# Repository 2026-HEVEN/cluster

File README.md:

# HEVEN Cluster 펌웨어

**2026 영광 대회 · 계기 클러스터(Instrument Cluster)** — ESP32가 CAN/BLE로 차량 상태(속도·전압·SOC·온도·에러)를 **받아서** LCD에 표현하고, 계기판 버튼 입력을 VCU로 보냅니다. PCB V3에서는 VESS PWM도 Cluster가 직접 출력합니다. VCU와 달리 **안전 임계가 약한 표시 전용 보드**입니다.

> 🤖 **AI 에이전트/팀원은 [`AGENTS.md`](AGENTS.md)를 먼저 읽으세요** — 무엇을 고쳐도 되고 무엇을 건드리면 안 되는지 규칙이 있습니다.

---

## 한눈에

- **스택**: PlatformIO + Arduino-ESP32, TWAI(CAN), ILI9341 LCD. 화면은 **패널 독립적 1bpp 프레임버퍼**(위젯이 그림) + `display_blit`(ILI9341로 blit)
- **구조**: 잠긴 코어(CAN·프레임버퍼·blit) + 팀원이 채우는 순수 모듈(`src/modules/`). VCU와 **동일한 2층 설계**지만 안전 FSM·50ms 라이프 태스크가 없고 CAN은 **수신(RX) 위주**입니다.
- **상태**: ESP32 빌드 성공, 호스트 native 테스트 111개 통과

## 사용자 문서

- [계기판 기능 및 한계](docs/ui_report/REPORT.md)
- [계기판 사용설명서](docs/ui_report/USER_MANUAL.md)
- [추가 CAN 정보 및 실차 확인 사항](docs/ui_report/CAN_DATA_REQUIRED.md)

## 빠른 시작

```bash
# 1. 이 레포를 깨끗한 위치에 클론
git clone https://github.com/2026-HEVEN/cluster.git
cd cluster

# 2. PlatformIO 설치 (한 번만) — VS Code면 PlatformIO IDE 확장 설치로 대체 가능
uv tool install platformio      # 또는: pipx install platformio

# 3. 노트북에서 테스트 (하드웨어 불필요)
pio test -e native

# 4. 보드에 빌드 & 업로드 (ESP32 연결 상태에서)
pio run -e esp32dev -t upload
```

> 🧪 **테스트가 처음이거나 Windows 사용자라면** → 노션 [펌웨어 테스트 실행 방법](https://www.notion.so/390913e532e68199a9b5e340b73e9e71) 참고. AI에 복붙할 프롬프트 + "이렇게 나오면 성공" 출력 예시 + Windows(WSL2/MinGW) 셋업까지 있습니다. (보드 업로드는 Windows도 그냥 되고, `native` 단위테스트만 host 컴파일러가 필요해요.)

> ℹ️ 모터컨트롤러 값은 MCU→VCU 피드백 프레임을 Cluster가 같은 CAN 버스에서 수신합니다. BMS SOC는 `LWS-1608` BLE BMS에 Cluster ESP32가 직접 연결해 표시용 telemetry로만 읽습니다.
> ℹ️ 계기판 속도 표시는 VCU가 내부 `vehicle_speed_compute()`로 산출한 단일 차량속도 프레임 `0x1803C0D0`을 사용합니다. 이 값은 전륜 기준 보정 로직을 거친 `km/h x 10` 값이며, Cluster는 다시 네 바퀴 평균을 내지 않습니다.
> ℹ️ GPS Lap Start는 현재 GNSS fix 위치를 출발점으로 저장합니다. 이후 VCU 단일 차량속도 `0.5 km/h` 초과가 `150ms` 이상 지속되면 랩타이머를 시작하고, 다시 출발점 반경 `2.0m` 안으로 들어오면 랩을 갱신합니다.

## 현재 하드웨어 핀맵 (PCB V3)

| 구분 | 기능 | ESP32 GPIO | 연결/동작 |
|------|------|------------|-----------|
| CAN | TXD | GPIO13 | CAN 트랜시버 TXD |
| CAN | RXD | GPIO14 | CAN 트랜시버 RXD |
| LCD ILI9341 | CS / RST / DC | GPIO23 / 22 / 21 | LCD 제어 |
| LCD / Touch SPI | MOSI / SCK / MISO | GPIO17 / 18 / 35 | 공용 SPI |
| LCD Touch XPT2046 | T_CS | GPIO16 | Touch chip select |
| GPS ZED-F9P | RX / TX / PPS | GPIO25 / 26 / 27 | 115200 baud NMEA/UBX, RTCM3 및 PPS |
| VESS | PWM | GPIO4 | 반전 MOSFET 구동, 50Hz 고정. 외부 RX-TH에는 1~2ms High 펄스 출력 |
| HMI | TV | GPIO32 | 토글 스위치, PCB 외부 10k 풀업, ON=LOW |
| HMI | Paddock | GPIO33 | 토글 스위치, PCB 외부 10k 풀업, ON=LOW |
| HMI | HOME | GPIO19 | 순간 푸시 버튼, PCB 외부 10k 풀업, ON=LOW |
| HMI | GPS Lap | GPIO5 | 순간 푸시 버튼, PCB 외부 10k 풀업, ON=LOW |
| HMI | Regen bit0 / bit1 | GPIO36 / 39 | 로터리, ON=LOW, 두 핀 모두 외부 풀업 필요 |
| Sense | START_IN | GPIO34 | 시동 전원 감지 ADC. 버튼 출력 핀이 아님 |

GPS TX2는 PCB V3에서 Cluster ESP32 `GPIO25` RX에 연결한다.

Cluster는 부팅 시 ZED-F9P UART1/UART2가 460800 baud로 설정되어 있더라도 UBX 설정으로 115200 baud로 낮춘 뒤 통신한다. NMEA가 끊기면 115200 baud 복구를 다시 시도하므로, 같은 GPS TX에 연결된 외부 로거도 115200 baud로 유지할 수 있다.

RTK 사용 시 Cluster ESP32가 Wi-Fi로 NTRIP caster에 접속하고, 수신한 RTCM3 바이트를 가공 없이 `GPIO26` UART TX로 ZED-F9P RX2에 전달한다. 실제 Wi-Fi/NTRIP 계정정보는 `include/ntrip_secrets.h`에 넣고 Git에는 올리지 않는다. `include/ntrip_secrets.example.h`를 복사해서 사용한다.

Cluster는 ZED-F9P RMC의 Speed Over Ground를 km/h로 변환해 새 RMC마다 Extended CAN `0x18F9FFC0`으로 송신한다. 속도는 0.01 km/h/bit이며 같은 프레임에 RMC fresh, GPS fix, RTK FLOAT/FIXED, speed valid, GGA quality와 RMC age를 포함한다. 상세 byte layout은 `docs/CAN_PROTOCOL.md`를 따른다.

회생제동 입력은 GPIO36/39 두 비트 로터리다. 0단은 OFF, 1~3단은 모두 같은 ON 요청으로 인코딩한다. 실제 회생 가능 여부와 전류 제한은 VCU가 최종 판단한다.

GPIO15는 현재 펌웨어에서 사용하지 않는다. GPIO15는 strapping pin이므로 외부 회로가 부팅 순간 강하게 잡아당기지 않게 주의한다.

GPIO34는 PCB V3의 START_IN 전원 감지 ADC다. 5ms마다 분압된 핀 전압을 읽고, 1.5V 이상에서 ON, 1.0V 이하에서 OFF로 판정하며 20ms 디바운스를 적용한다. 이 값은 Car Check의 VCU/SENSOR 상세 화면에 표시할 뿐 차량 제어에는 사용하지 않는다. 기어는 VCU에서 읽는다.
## 어디서 작업하나

| 폴더 | 내용 | 편집? |
|------|------|-------|
| `src/modules/` | 순수 계산 함수 `xxx_compute()` | ✅ **여기서만** |
| `test/` | 노트북 단위 테스트 | ✅ |
| `src/core/`, `src/logic/`, `include/` | CAN·framebuffer·display_blit·스케줄러·타입 | 🔒 잠김 |
| `platformio.ini`, `src/main.cpp` | 빌드 설정·진입점 | 🔒 잠김 |

새 모듈을 추가하거나 기존 `compute()`를 채우는 법 → [`docs/ADDING_A_MODULE.md`](docs/ADDING_A_MODULE.md)

## 모듈 목록 (FILL-IN)

- `hmi_input` — config 스위치(패독·TC·회생·디버그) → `ClusterCommand` (CAN으로 VCU에 전송)
- `widgets/` — 계기판 화면 위젯 (speed·battery·warnings·gear ...). 1bpp 프레임버퍼에 그림.
  새 위젯 추가법: `docs/ADDING_A_WIDGET.md`

> 표시는 패널 독립적 **1bpp 프레임버퍼**로. 실제 패널 blit(`display_blit`)은 하드웨어 확정 후 구현.

## 문서

| 문서 | 내용 |
|------|------|
| [`AGENTS.md`](AGENTS.md) / `CLAUDE.md` | 작업 규칙 (에이전트·팀원 필독) |
| [`docs/ADDING_A_MODULE.md`](docs/ADDING_A_MODULE.md) | 모듈 추가/작성 절차 |
| [`docs/CAN_PROTOCOL.md`](docs/CAN_PROTOCOL.md) | CAN 메시지 명세 (VCU/Cluster 공유 단일 출처) |

> 전체 설계 원리(compute/update 분리, state 격리, 테스트 등)는 **VCU 레포의 [`ARCHITECTURE.md`](https://github.com/2026-HEVEN/vcu/blob/main/docs/ARCHITECTURE.md)** 와 동일합니다.

## 아직 미구현 (의도된 TODO)

- **VCU 표시 상태 프레임 구현** — VCU가 `0x1801C0D0`으로 확정 기어/HV/브레이크 상태를 보내면 Cluster가 그 값을 우선 표시합니다.
- **BMS BLE 실차 검증** — `LWS-1608` BLE 이름, `FFE0/FFE1/FFE2` 특성, SOC/current 부호를 실제 배터리팩에서 확인해야 합니다.

## 버전 기록 (Changelog)

> 각 버전은 git 태그로도 관리됩니다 → [GitHub Releases](https://github.com/2026-HEVEN/cluster/releases)
> **새 버전 올릴 때:** 아래에 항목 추가 → `git tag vX.Y` → `git push origin vX.Y`.

### v1.1.1 (2026-07-06) — 위젯 레이아웃 렌더 테스트
- `test/test_render_layout`: `app_wiring.cpp`의 위젯 배치를 그대로 재현해 24bit BMP로 덤프하는 시각화 테스트 추가. `pio test -e native -f test_render_layout` 로 실행 → `render_layout.bmp` 생성(Windows 사진 앱/그림판 등 추가 도구 없이 바로 열림), 위젯별 할당 공간을 박스로 표시
- `.gitignore`에 `*.bmp` 추가

### v1.1 (2026-06-29) — 디스플레이 프레임버퍼 재설계
- 패널 독립적 **1bpp 프레임버퍼**(320×160) + 위젯 모듈(speed · battery · warnings · gear) 도입 — 렌더링을 모듈로 넘겨 자유도↑, host 테스트 가능(ASCII 시각화)
- `hmi_input` → **`ClusterCommand`**(paddock · TC · regen · debug) 의미 커맨드 패턴, **패독 모드** 추가
- **제거**: `vess`, `indicators`, `display_render`(U8g2), `io_expander`(MCP23017)
- `display_blit` stub(패널 확정 후 구현), CAN 커맨드 레이아웃(`CAN_PROTOCOL.md` §5.7) 갱신

### v1.0 (2026-06-29) — 초기 Cluster 펌웨어 베이스
- 잠긴 코어(CAN RX · MCP23017 · U8g2 OLED) + 순수 모듈(display · indicators · vess · hmi_input)
- PlatformIO native 테스트, AGENTS/ADDING_A_MODULE/CAN_PROTOCOL 문서

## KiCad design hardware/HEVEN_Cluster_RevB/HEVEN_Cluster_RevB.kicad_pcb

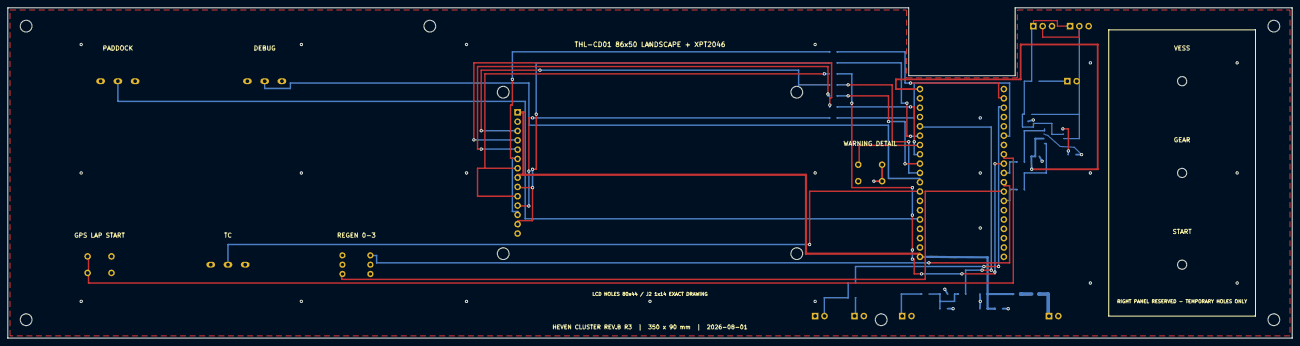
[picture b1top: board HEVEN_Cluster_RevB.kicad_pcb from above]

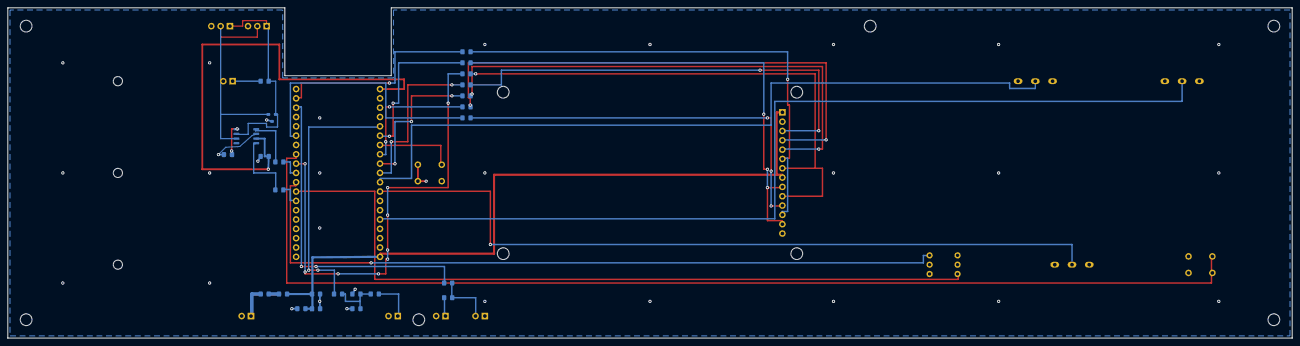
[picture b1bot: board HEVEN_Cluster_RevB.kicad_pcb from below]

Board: 2 copper layers, 350.0 x 90.0 mm, 49 parts (26 on the bottom side), 40 nets.

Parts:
C_CAN: 100nF; C_0805
C_LV: 100nF; C_0805
C_PWR_BULK: 100uF; C_0805
C_PWR_HF: 100nF; C_0805_R180
D_CAN: PESD1CAN; SOT23_CAN_ESD
D_REV: SS34; R_0805
D_TVS5: SMBJ5.0A; C_0805_R180
F1: PTC 1.1A; R_0805
H1, H2, H3, H4, H5, H6: M3; MountingHole_M3
H_GEAR: GEAR temporary; Temporary_Panel_Hole
H_START: START temporary; Temporary_Panel_Hole
H_VESS: VESS temporary; Temporary_Panel_Hole
JP_TERM: 120R termination enable; PinHeader_1x2_P2.54
J_CAN_TMA: CANH,CANL,GND; PinHeader_1x3_P2.54
J_CAN_VEH: CANH,CANL,GND; PinHeader_1x3_P2.54
J_GPS: GPS external: GND,TX2; PinHeader_1x2_P2.54
J_LV: LV12 sense,GND; PinHeader_1x2_P2.54
J_PWR: 5V input,GND; PinHeader_1x2_P2.54
J_TMA_GPS: TMA GPS RX,GND; PinHeader_1x2_P2.54
LCD1: THL-CD01 ILI9341+XPT2046 86x50 LANDSCAPE; LCD_THL_CD01_Landscape
R_CANRX: 33R; R_0805
R_CANTX: 33R; R_0805
R_CAN_RS: 10k; R_0805
R_GPS_ESP: 220R; R_0805
R_GPS_TMA: 220R; R_0805
R_LCD_CS: 33R; R_0805
R_LCD_DC: 33R; R_0805
R_LCD_MISO: 33R; R_0805
R_LCD_MOSI: 33R; R_0805
R_LCD_RST: 33R; R_0805
R_LCD_SCK: 33R; R_0805
R_LV_BOT: 27k; R_0805
R_LV_SER: 1k; R_0805
R_LV_TOP: 100k; R_0805
R_TERM: 120R; R_0805
R_TOUCH_CS: 33R; R_0805
SW_DEBUG: MTS-102; SW_Toggle_MTS_102
SW_LAP: NW3-TS-D001 H9; SW_Tact_NW3_TS_D001_H9
SW_PADDOCK: MTS-102; SW_Toggle_MTS_102
SW_REGEN: SDR-04 4-position binary; SW_Rotary_SDR_04
SW_TC: MTS-102; SW_Toggle_MTS_102
SW_WARN: NW3-TS-D001 H9; SW_Tact_NW3_TS_D001_H9
U_CAN: SN65HVD230D; SOIC8_SN65HVD230
U_ESP: Keyestudio ESP32-WROOM-32E USB-C 38pin; ESP32_DevBoard_38Pin_USB_C

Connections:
3V3: C_CAN.1, U_CAN.3, U_ESP.1
5V_FUSED: D_REV.2, F1.1
5V_IN: F1.2, J_PWR.1
5V_SYS: C_PWR_BULK.1, C_PWR_HF.1, D_REV.1, D_TVS5.1, LCD1.1, LCD1.8, U_ESP.19
CAN_H: D_CAN.1, J_CAN_TMA.1, J_CAN_VEH.1, R_TERM.1, U_CAN.7
CAN_L: D_CAN.3, JP_TERM.2, J_CAN_TMA.2, J_CAN_VEH.2, U_CAN.6
CAN_RS: R_CAN_RS.1, U_CAN.8
CAN_RX_IC: R_CANRX.2, U_CAN.4
CAN_RX_MCU: R_CANRX.1, U_ESP.32
CAN_TX_IC: R_CANTX.2, U_CAN.1
CAN_TX_MCU: R_CANTX.1, U_ESP.29
DEBUG: SW_DEBUG.2, U_ESP.11
GND: C_CAN.2, C_LV.2, C_PWR_BULK.2, C_PWR_HF.2, D_CAN.2, D_TVS5.2, J_CAN_TMA.3, J_CAN_VEH.3, J_GPS.1, J_LV.2, J_PWR.2, J_TMA_GPS.2, LCD1.2, R_CAN_RS.2, R_LV_BOT.2, SW_DEBUG.1, SW_LAP.2, SW_PADDOCK.1, SW_REGEN.C, SW_TC.1, SW_WARN.2, U_CAN.2, U_ESP.20, U_ESP.26
GPS_LAP_START: SW_LAP.1, U_ESP.27
GPS_RX_MCU: R_GPS_ESP.2, U_ESP.22
GPS_TMA: J_TMA_GPS.1, R_GPS_TMA.2
GPS_TX_RAW: J_GPS.2, R_GPS_ESP.1, R_GPS_TMA.1
LCD_CS: LCD1.3, R_LCD_CS.1
LCD_CS_MCU: R_LCD_CS.2, U_ESP.10
LCD_DC: LCD1.5, R_LCD_DC.1
LCD_DC_MCU: R_LCD_DC.2, U_ESP.9
LCD_MISO: LCD1.9, LCD1.13, R_LCD_MISO.1
LCD_MISO_MCU: R_LCD_MISO.2, U_ESP.6
LCD_MOSI: LCD1.6, LCD1.12, R_LCD_MOSI.1
LCD_MOSI_MCU: R_LCD_MOSI.2, U_ESP.21
LCD_RST: LCD1.4, R_LCD_RST.1
LCD_RST_MCU: R_LCD_RST.2, U_ESP.8
LCD_SCK: LCD1.7, LCD1.10, R_LCD_SCK.1
LCD_SCK_MCU: R_LCD_SCK.2, U_ESP.28
LV12_SENSE: J_LV.1, R_LV_TOP.1
LV_ADC: R_LV_SER.2, U_ESP.5
LV_DIV: C_LV.1, R_LV_BOT.1, R_LV_SER.1, R_LV_TOP.2
PADDOCK: SW_PADDOCK.2, U_ESP.15
REGEN_BIT0: SW_REGEN.1, U_ESP.31
REGEN_BIT1: SW_REGEN.2, U_ESP.30
TC: SW_TC.2, U_ESP.12
TERM_NODE: JP_TERM.1, R_TERM.2
TOUCH_CS: LCD1.11, R_TOUCH_CS.1
TOUCH_CS_MCU: R_TOUCH_CS.2, U_ESP.25
WARNING_DETAIL: SW_WARN.1, U_ESP.7

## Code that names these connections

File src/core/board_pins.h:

#pragma once

// Physical Cluster PCB V3 pin map.
// Source of truth: Notion "PCB V3 설계" (2026-09-17).
namespace board_pins {
constexpr int LCD_CS = 23;
constexpr int LCD_RST = 22;
constexpr int LCD_DC = 21;
constexpr int SPI_MOSI = 17;
constexpr int SPI_SCK = 18;
constexpr int SPI_MISO = 35;
constexpr int TOUCH_CS = 16;

constexpr int CAN_RX = 14;
constexpr int CAN_TX = 13;

constexpr int GNSS_RX = 25;
constexpr int GNSS_TX = 26;
constexpr int GNSS_PPS = 27;

constexpr int VESS_PWM = 4;
constexpr int TV_SWITCH = 32;
constexpr int PADDOCK_SWITCH = 33;
constexpr int HOME_BUTTON = 19;
constexpr int LAP_BUTTON = 5;
constexpr int REGEN_BIT0 = 36;
constexpr int REGEN_BIT1 = 39;
constexpr int START_SENSE_ADC = 34;
} // namespace board_pins
